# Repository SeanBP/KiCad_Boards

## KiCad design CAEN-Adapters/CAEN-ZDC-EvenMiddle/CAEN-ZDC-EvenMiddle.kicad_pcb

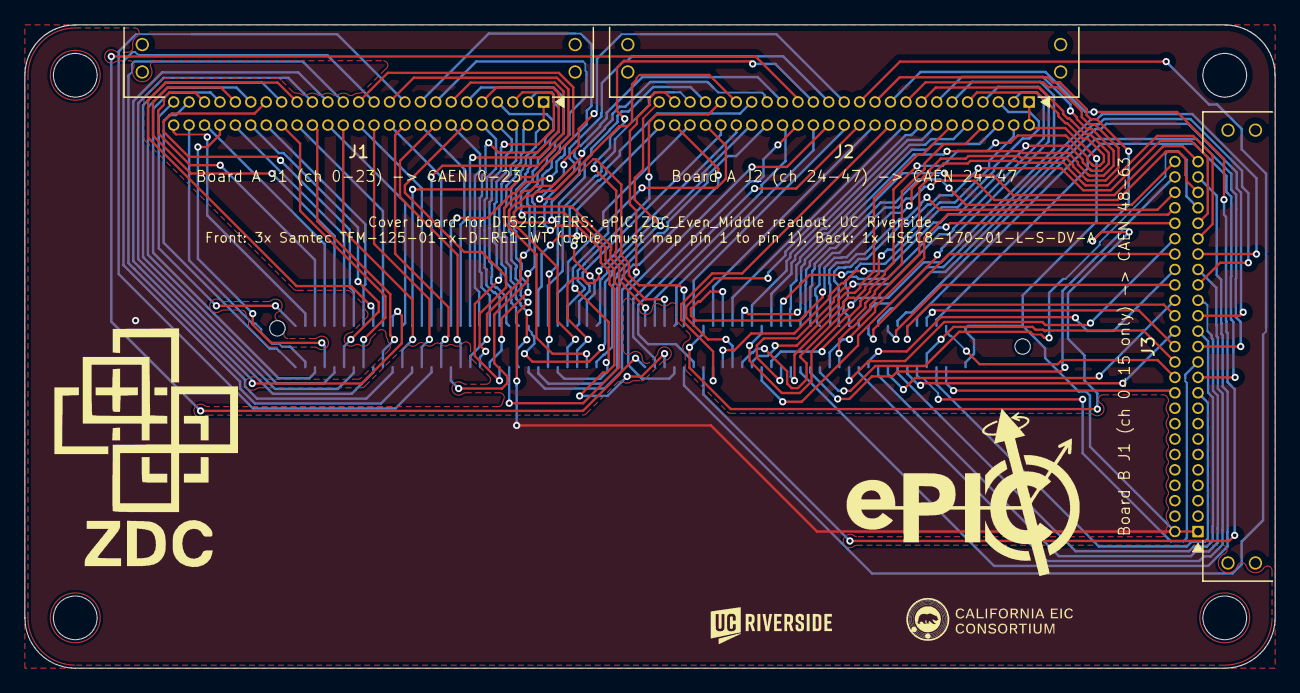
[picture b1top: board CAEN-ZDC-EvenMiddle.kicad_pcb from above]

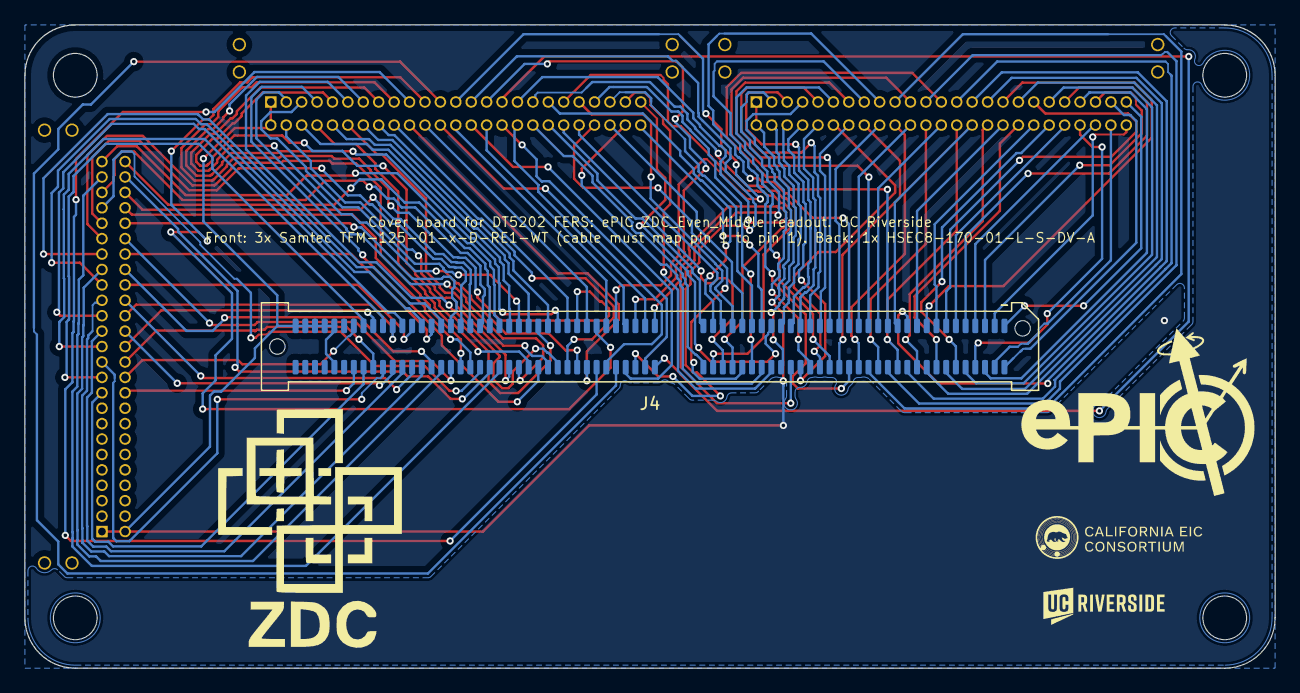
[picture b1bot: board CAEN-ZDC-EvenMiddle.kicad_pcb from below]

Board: 2 copper layers, 103.0 x 53.0 mm, 12 parts (5 on the bottom side), 129 nets.

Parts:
J1, J2, J3: Samtec_TFM-125-01-x-D-RE1-WT_2x25_P1.27mm_Horizon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; Samtec_TFM-125-01-x-D-RE1-WT_2x25_P1.27mm_Horizontal
J4: Samtec_HSEC8-170-01-X-DV-A_2x70_P0.8mm_Pol32_Sock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; Samtec_HSEC8-170-01-X-DV-A_2x70_P0.8mm_Pol32_Socket_Alignme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
LOGO1, LOGO7: LOGO
LOGO2, LOGO8: LOGO; UCR_Logo_1cm
LOGO3, LOGO6: LOGO; LOGO_ZDC_mark
LOGO4, LOGO5: LOGO; Consortium_logo_1pt4cm

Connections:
A0: J1.49, J4.1
A1: J1.47, J4.2
A2: J1.45, J4.5
A3: J1.43, J4.6
A4: J1.41, J4.9
A5: J1.39, J4.10
A6: J1.37, J4.13
A7: J1.35, J4.14
A8: J1.33, J4.17
A9: J1.31, J4.18
A10: J1.29, J4.21
A11: J1.27, J4.22
A12: J1.25, J4.25
A13: J1.23, J4.26
A14: J1.21, J4.29
A15: J1.19, J4.30
A16: J1.17, J4.33
A17: J1.15, J4.34
A18: J1.13, J4.37
A19: J1.11, J4.38
A20: J1.9, J4.41
A21: J1.7, J4.42
A22: J1.5, J4.45
A23: J1.3, J4.46
A24: J2.49, J4.49
A25: J2.47, J4.50
A26: J2.45, J4.53
A27: J2.43, J4.54
A28: J2.41, J4.57
A29: J2.39, J4.58
A30: J2.37, J4.61
A31: J2.35, J4.62
A32: J2.33, J4.65
A33: J2.31, J4.66
A34: J2.29, J4.69
A35: J2.27, J4.70
A36: J2.25, J4.73
A37: J2.23, J4.74
A38: J2.21, J4.77
A39: J2.19, J4.78
A40: J2.17, J4.81
A41: J2.15, J4.82
A42: J2.13, J4.85
A43: J2.11, J4.86
A44: J2.9, J4.89
A45: J2.7, J4.90
A46: J2.5, J4.93
A47: J2.3, J4.94
A48: J3.49, J4.97
A49: J3.47, J4.98
A50: J3.45, J4.101
A51: J3.43, J4.102
A52: J3.41, J4.105
A53: J3.39, J4.106
A54: J3.37, J4.109
A55: J3.35, J4.110
A56: J3.33, J4.113
A57: J3.31, J4.114
A58: J3.29, J4.117
A59: J3.27, J4.118
A60: J3.25, J4.121
A61: J3.23, J4.122
A62: J3.21, J4.125
A63: J3.19, J4.126
GND: J1.1, J1.2, J2.1, J2.2, J3.1, J3.2, J4.131, J4.132, J4.133, J4.135, J4.137, J4.139
K0: J1.50, J4.3
K1: J1.48, J4.4
K2: J1.46, J4.7
K3: J1.44, J4.8
K4: J1.42, J4.11
K5: J1.40, J4.12
K6: J1.38, J4.15
K7: J1.36, J4.16
K8: J1.34, J4.19
K9: J1.32, J4.20
K10: J1.30, J4.23
K11: J1.28, J4.24
K12: J1.26, J4.27
K13: J1.24, J4.28
K14: J1.22, J4.31
K15: J1.20, J4.32
K16: J1.18, J4.35
K17: J1.16, J4.36
K18: J1.14, J4.39
K19: J1.12, J4.40
K20: J1.10, J4.43
K21: J1.8, J4.44
K22: J1.6, J4.47
K23: J1.4, J4.48
K24: J2.50, J4.51
K25: J2.48, J4.52
K26: J2.46, J4.55
K27: J2.44, J4.56
K28: J2.42, J4.59
K29: J2.40, J4.60
K30: J2.38, J4.63
K31: J2.36, J4.64
K32: J2.34, J4.67
K33: J2.32, J4.68
K34: J2.30, J4.71
K35: J2.28, J4.72
K36: J2.26, J4.75
K37: J2.24, J4.76
K38: J2.22, J4.79
K39: J2.20, J4.80
K40: J2.18, J4.83
K41: J2.16, J4.84
K42: J2.14, J4.87
K43: J2.12, J4.88
K44: J2.10, J4.91
K45: J2.8, J4.92
K46: J2.6, J4.95
K47: J2.4, J4.96
K48: J3.50, J4.99
K49: J3.48, J4.100
K50: J3.46, J4.103
K51: J3.44, J4.104
K52: J3.42, J4.107
K53: J3.40, J4.108
K54: J3.38, J4.111
K55: J3.36, J4.112
K56: J3.34, J4.115
K57: J3.32, J4.116
K58: J3.30, J4.119
K59: J3.28, J4.120
K60: J3.26, J4.123
K61: J3.24, J4.124
K62: J3.22, J4.127
K63: J3.20, J4.128

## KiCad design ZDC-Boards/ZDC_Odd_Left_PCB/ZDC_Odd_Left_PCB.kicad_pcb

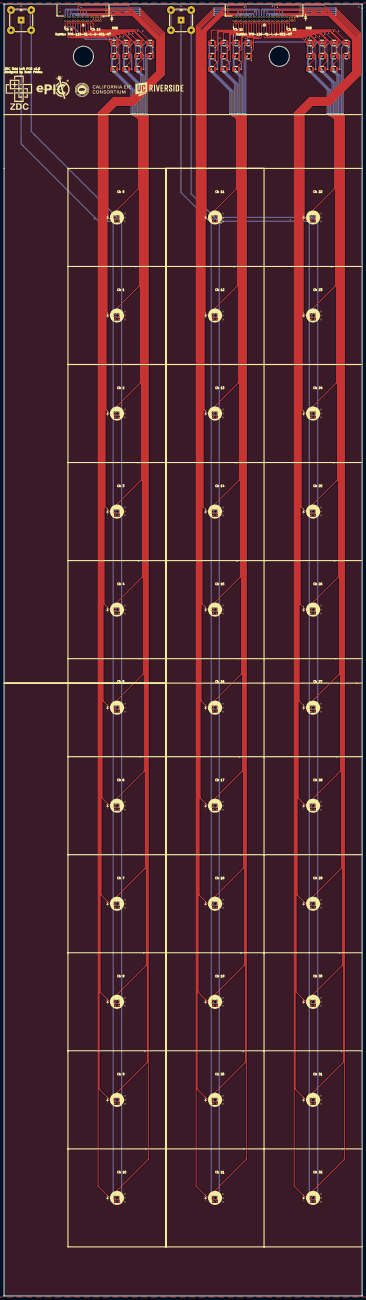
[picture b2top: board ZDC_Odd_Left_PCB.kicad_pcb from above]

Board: 2 copper layers, 178.2 x 643.0 mm, 70 parts (0 on the bottom side), 69 nets.

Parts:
C0, C1, C2, C3, C4, C5, C6, C7, C8, C9, C10, C11, C12, C13, C14, C15, C16, C17, C18, C19, C20, C21, C22, C23, C24, C25, C26, C27, C28, C29, C30, C31, C32: C_1210_3225Metric
D0, D1, D2, D3, D4, D5, D6, D7, D8, D9, D10, D11, D12, D13, D14, D15, D16, D17, D18, D19, D20, D21, D22, D23, D24, D25, D26, D27, D28, D29, D30, D31, D32: S14160-3015PS; S14160-1315PS_dimple_silkscreen_with_capacitor
J1: Samtec_TFM-115-01-x-D-RE1-WT_2x15_P1.27mm_Horizon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; Samtec_TFM-115-01-x-D-RE1-WT_2x15_P1.27mm_Horizontal
J2: Samtec_TFM-125-01-x-D-RE1-WT_2x25_P1.27mm_Horizon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; Samtec_TFM-125-01-x-D-RE1-WT_2x25_P1.27mm_Horizontal
J3, J4: BNC_TEConnectivity_1478035_Horizontal

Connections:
A0: D0.8, J1.29
A1: D1.8, J1.27
A2: D2.8, J1.25
A3: D3.8, J1.23
A4: D4.8, J1.21
A5: D5.8, J1.19
A6: D6.8, J1.17
A7: D7.8, J1.15
A8: D8.8, J1.13
A9: D9.8, J1.11
A10: D10.8, J1.9
A11: D11.8, J2.49
A12: D12.8, J2.47
A13: D13.8, J2.45
A14: D14.8, J2.43
A15: D15.8, J2.41
A16: D16.8, J2.39
A17: D17.8, J2.37
A18: D18.8, J2.35
A19: D19.8, J2.33
A20: D20.8, J2.31
A21: D21.8, J2.29
A22: D22.8, J2.27
A23: D23.8, J2.25
A24: D24.8, J2.23
A25: D25.8, J2.21
A26: D26.8, J2.19
A27: D27.8, J2.17
A28: D28.8, J2.15
A29: D29.8, J2.13
A30: D30.8, J2.11
A31: D31.8, J2.9
A32: D32.8, J2.7
GND: C0.2, C1.2, C2.2, C3.2, C4.2, C5.2, C6.2, C7.2, C8.2, C9.2, C10.2, C11.2, C12.2, C13.2, C14.2, C15.2, C16.2, C17.2, C18.2, C19.2, C20.2, C21.2, C22.2, C23.2, C24.2, C25.2, C26.2, C27.2, C28.2, C29.2, C30.2, C31.2, C32.2, J1.1, J1.2, J1.3, J1.4, J1.5, J1.6, J1.7, J1.8, J1.MP, J2.1, J2.2, J2.3, J2.4, J2.5, J2.6, J2.MP
K0: C0.1, D0.7, J1.30
K1: C1.1, D1.7, J1.28
K2: C2.1, D2.7, J1.26
K3: C3.1, D3.7, J1.24
K4: C4.1, D4.7, J1.22
K5: C5.1, D5.7, J1.20
K6: C6.1, D6.7, J1.18
K7: C7.1, D7.7, J1.16
K8: C8.1, D8.7, J1.14
K9: C9.1, D9.7, J1.12
K10: C10.1, D10.7, J1.10
K11: C11.1, D11.7, J2.50
K12: C12.1, D12.7, J2.48
K13: C13.1, D13.7, J2.46
K14: C14.1, D14.7, J2.44
K15: C15.1, D15.7, J2.42
K16: C16.1, D16.7, J2.40
K17: C17.1, D17.7, J2.38
K18: C18.1, D18.7, J2.36
K19: C19.1, D19.7, J2.34
K20: C20.1, D20.7, J2.32
K21: C21.1, D21.7, J2.30
K22: C22.1, D22.7, J2.28
K23: C23.1, D23.7, J2.26
K24: C24.1, D24.7, J2.24
K25: C25.1, D25.7, J2.22
K26: C26.1, D26.7, J2.20
K27: C27.1, D27.7, J2.18
K28: C28.1, D28.7, J2.16
K29: C29.1, D29.7, J2.14
K30: C30.1, D30.7, J2.12
K31: C31.1, D31.7, J2.10
K32: C32.1, D32.7, J2.8
LA1: D0.9, D1.9, D2.9, D3.9, D4.9, D5.9, D6.9, D7.9, D8.9, D9.9, D10.9, J3.1
LA2: D11.9, D12.9, D13.9, D14.9, D15.9, D16.9, D17.9, D18.9, D19.9, D20.9, D21.9, D22.9, D23.9, D24.9, D25.9, D26.9, D27.9, D28.9, D29.9, D30.9, D31.9, D32.9, J4.1

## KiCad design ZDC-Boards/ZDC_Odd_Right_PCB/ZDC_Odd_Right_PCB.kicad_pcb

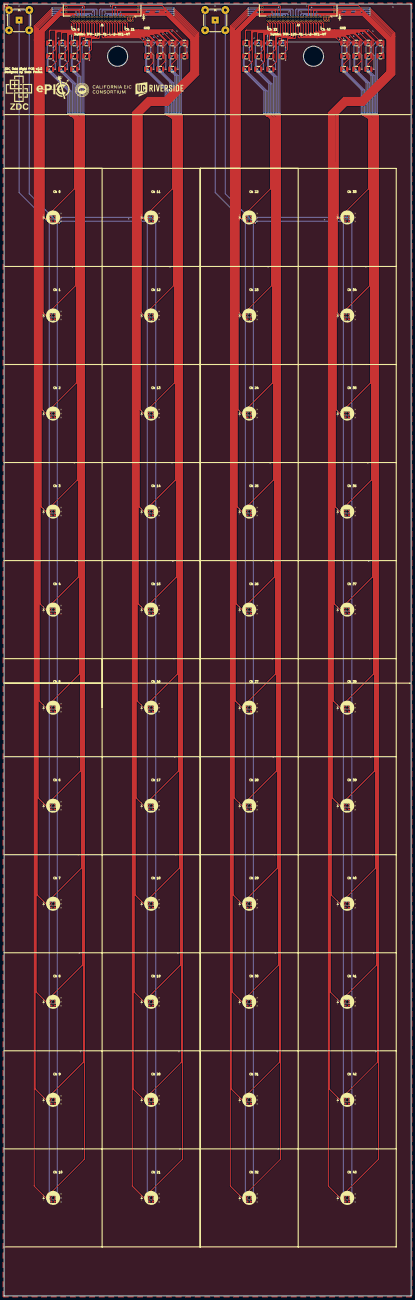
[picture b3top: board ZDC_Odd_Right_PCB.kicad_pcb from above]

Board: 2 copper layers, 202.6 x 643.0 mm, 92 parts (0 on the bottom side), 91 nets.

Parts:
C0, C1, C2, C3, C4, C5, C6, C7, C8, C9, C10, C11, C12, C13, C14, C15, C16, C17, C18, C19, C20, C21, C22, C23, C24, C25, C26, C27, C28, C29, C30, C31, C32, C33, C34, C35, C36, C37, C38, C39, C40, C41, C42, C43: C_1210_3225Metric
D0, D1, D2, D3, D4, D5, D6, D7, D8, D9, D10, D11, D12, D13, D14, D15, D16, D17, D18, D19, D20, D21, D22, D23, D24, D25, D26, D27, D28, D29, D30, D31, D32, D33, D34, D35, D36, D37, D38, D39, D40, D41, D42, D43: S14160-3015PS; S14160-1315PS_dimple_silkscreen_with_capacitor
J1, J2: Samtec_TFM-125-01-x-D-RE1-WT_2x25_P1.27mm_Horizon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; Samtec_TFM-125-01-x-D-RE1-WT_2x25_P1.27mm_Horizontal
J3: BNC_TEConnectivity_1478035_Horizontal; BNC_TEConnectivity_1478035_Horizontal_EdgePads
J4: BNC_TEConnectivity_1478035_Horizontal

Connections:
A0: D0.8, J1.49
A1: D1.8, J1.47
A2: D2.8, J1.45
A3: D3.8, J1.43
A4: D4.8, J1.41
A5: D5.8, J1.39
A6: D6.8, J1.37
A7: D7.8, J1.35
A8: D8.8, J1.33
A9: D9.8, J1.31
A10: D10.8, J1.29
A11: D11.8, J1.27
A12: D12.8, J1.25
A13: D13.8, J1.23
A14: D14.8, J1.21
A15: D15.8, J1.19
A16: D16.8, J1.17
A17: D17.8, J1.15
A18: D18.8, J1.13
A19: D19.8, J1.11
A20: D20.8, J1.9
A21: D21.8, J1.7
A22: D22.8, J2.49
A23: D23.8, J2.47
A24: D24.8, J2.45
A25: D25.8, J2.43
A26: D26.8, J2.41
A27: D27.8, J2.39
A28: D28.8, J2.37
A29: D29.8, J2.35
A30: D30.8, J2.33
A31: D31.8, J2.31
A32: D32.8, J2.29
A33: D33.8, J2.27
A34: D34.8, J2.25
A35: D35.8, J2.23
A36: D36.8, J2.21
A37: D37.8, J2.19
A38: D38.8, J2.17
A39: D39.8, J2.15
A40: D40.8, J2.13
A41: D41.8, J2.11
A42: D42.8, J2.9
A43: D43.8, J2.7
GND: C0.2, C1.2, C2.2, C3.2, C4.2, C5.2, C6.2, C7.2, C8.2, C9.2, C10.2, C11.2, C12.2, C13.2, C14.2, C15.2, C16.2, C17.2, C18.2, C19.2, C20.2, C21.2, C22.2, C23.2, C24.2, C25.2, C26.2, C27.2, C28.2, C29.2, C30.2, C31.2, C32.2, C33.2, C34.2, C35.2, C36.2, C37.2, C38.2, C39.2, C40.2, C41.2, C42.2, C43.2, J1.1, J1.2, J1.3, J1.4, J1.5, J1.6, J1.MP, J2.1, J2.2, J2.3, J2.4, J2.5, J2.6, J2.MP
K0: C0.1, D0.7, J1.50
K1: C1.1, D1.7, J1.48
K2: C2.1, D2.7, J1.46
K3: C3.1, D3.7, J1.44
K4: C4.1, D4.7, J1.42
K5: C5.1, D5.7, J1.40
K6: C6.1, D6.7, J1.38
K7: C7.1, D7.7, J1.36
K8: C8.1, D8.7, J1.34
K9: C9.1, D9.7, J1.32
K10: C10.1, D10.7, J1.30
K11: C11.1, D11.7, J1.28
K12: C12.1, D12.7, J1.26
K13: C13.1, D13.7, J1.24
K14: C14.1, D14.7, J1.22
K15: C15.1, D15.7, J1.20
K16: C16.1, D16.7, J1.18
K17: C17.1, D17.7, J1.16
K18: C18.1, D18.7, J1.14
K19: C19.1, D19.7, J1.12
K20: C20.1, D20.7, J1.10
K21: C21.1, D21.7, J1.8
K22: C22.1, D22.7, J2.50
K23: C23.1, D23.7, J2.48
K24: C24.1, D24.7, J2.46
K25: C25.1, D25.7, J2.44
K26: C26.1, D26.7, J2.42
K27: C27.1, D27.7, J2.40
K28: C28.1, D28.7, J2.38
K29: C29.1, D29.7, J2.36
K30: C30.1, D30.7, J2.34
K31: C31.1, D31.7, J2.32
K32: C32.1, D32.7, J2.30
K33: C33.1, D33.7, J2.28
K34: C34.1, D34.7, J2.26
K35: C35.1, D35.7, J2.24
K36: C36.1, D36.7, J2.22
K37: C37.1, D37.7, J2.20
K38: C38.1, D38.7, J2.18
K39: C39.1, D39.7, J2.16
K40: C40.1, D40.7, J2.14
K41: C41.1, D41.7, J2.12
K42: C42.1, D42.7, J2.10
K43: C43.1, D43.7, J2.8
LA1: D0.9, D1.9, D2.9, D3.9, D4.9, D5.9, D6.9, D7.9, D8.9, D9.9, D10.9, D11.9, D12.9, D13.9, D14.9, D15.9, D16.9, D17.9, D18.9, D19.9, D20.9, D21.9, J3.1
LA2: D22.9, D23.9, D24.9, D25.9, D26.9, D27.9, D28.9, D29.9, D30.9, D31.9, D32.9, D33.9, D34.9, D35.9, D36.9, D37.9, D38.9, D39.9, D40.9, D41.9, D42.9, D43.9, J4.1

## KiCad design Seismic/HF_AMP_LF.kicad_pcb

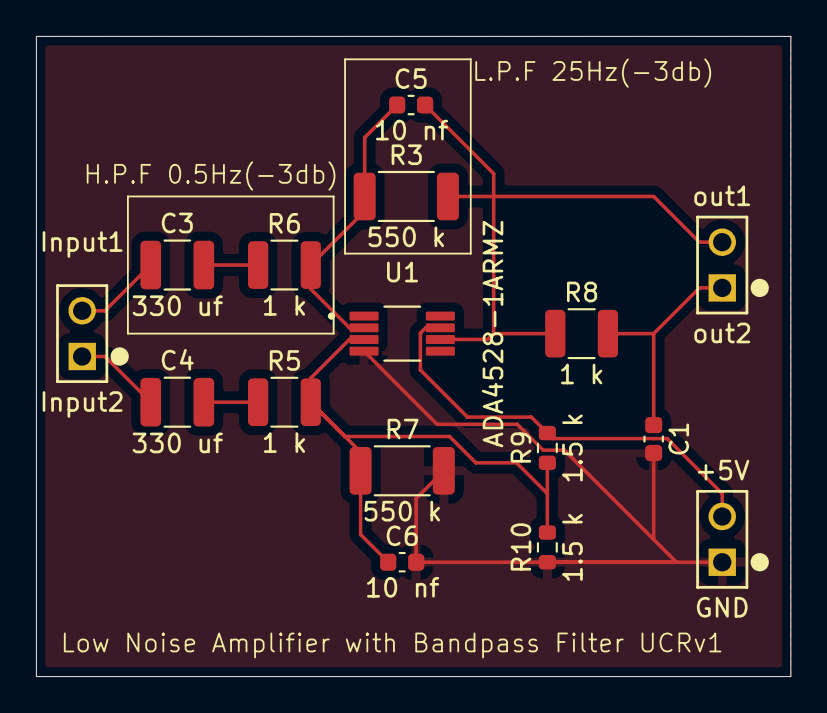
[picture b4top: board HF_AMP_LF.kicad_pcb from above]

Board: 2 copper layers, 41.9 x 35.6 mm, 13 parts (0 on the bottom side), 8 nets.

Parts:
C1: 1 uf; C_0603_1608Metric
C3, C4: 330 uf; C_1210_3225Metric
C5, C6: 10 nf; C_0603_1608Metric
R3, R7: 550 k; R_2010_5025Metric
R5, R6, R8: 1 k; R_1210_3225Metric
R9, R10: 1.5 k; R_0603_1608Metric
U1: ADA4528-1ARMZ; SOP65P490X110-8N

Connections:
+5V: R9.2, U1.7 (V+)
GND: C1.2, C6.2, R7.2, R10.1, U1.4 (V-)
unnamed: C1.1, R8.2
unnamed: C3.2, R6.1
unnamed: C4.2, R5.1
unnamed: C6.1, R5.2, R7.1, R9.1, R10.2, U1.3 (+IN)
unnamed: C5.1, R3.1, R6.2, U1.2 (-IN)
unnamed: C5.2, R3.2, R8.1, U1.6 (OUT)

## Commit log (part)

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2025-05-28 Updated PCBs to include temp sensors
2025-05-28 Finished CAEN adapter
2025-06-06 Updated boards
2025-08-08 Adding boards
2025-09-08 Updated boards with connector HSEC8-109-01-L-DV-A-BL
2025-09-08 Updated board names and images
2025-09-08 Added prototype boards
2025-09-09 Added CAEN-8ch-Old
2025-09-12 Fixed Gamma-32ch-3in
2025-10-10 Added CAEN-8ch-80mm
2025-10-10 Updated names for "old" CAEN adapters
2025-10-10 Added Muon-8ch-48.8mm-2mmSiPM
2025-10-10 Updated silkscreen with proper SiPM number S13360-2050VE
2025-10-14 Edge Card 9ch v2 + 9ch latch IV board v2 +
    Updated Edge Card 9ch to v2 with expanded pads, and fixed 9ch latch IV board to reroute one trace around a hole
2025-10-17 Fixed CAEN-8ch-80mm disconnected traces
2025-10-31 Added Edge-Card-CAEN
2026-01-26 Upload RJ45 connector boards and 16ch board with small tile.
2026-02-20 Included zip file with gerber outputs.
2026-02-20 Edge Card gerber file added
2026-03-25 Corrected channel 5 connection
2026-03-25 Fixed Samtec 10-pin connector for pinned sipms.
2026-04-01 Filter+Amplifier Board for reading sesmic output and output to Pi
2026-04-01 Included links to the model of the board used.
2026-04-03 fixed jlcpcb version
2026-06-17 Updated ZDC Boards to v1.0
2026-06-25 Updated small connector on ZDC PCBs
